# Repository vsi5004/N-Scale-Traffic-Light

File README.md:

# N-Scale-Traffic-Light
The PCB and 3D files for an accurately scaled 1:160 traffic light

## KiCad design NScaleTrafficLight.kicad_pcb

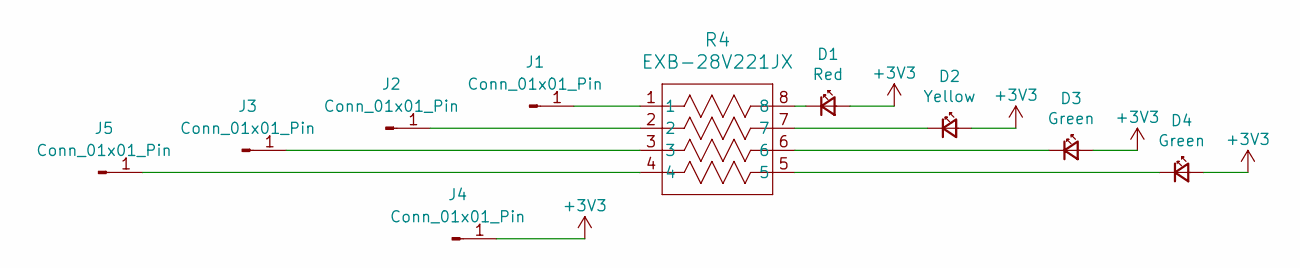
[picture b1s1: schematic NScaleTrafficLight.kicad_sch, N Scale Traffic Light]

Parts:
D1: Red; LED_0402_1005Metric; Mouser 710-150060VS55040
D2: Yellow; LED_0402_1005Metric; Mouser 710-150060VS55040
D3, D4: Green; LED_0402_1005Metric; Mouser 710-150060VS55040
J1, J2, J3, J4, J5: Conn_01x01_Pin; SolderWirePad_1x01_SMD_1x2mm
R4: EXB-28V221JX; EXB28V_PAN

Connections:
+3V3: D1.2 (A), D2.2 (A), D3.2 (A), D4.2 (A), J4.1
unnamed: D1.1 (K), R4.8
unnamed: D2.1 (K), R4.7
unnamed: D3.1 (K), R4.6
unnamed: D4.1 (K), R4.5
unnamed: J1.1, R4.1
unnamed: J2.1, R4.2
unnamed: J3.1, R4.3
unnamed: J5.1, R4.4

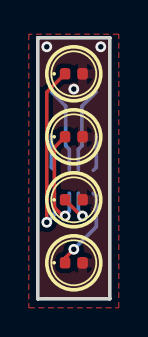
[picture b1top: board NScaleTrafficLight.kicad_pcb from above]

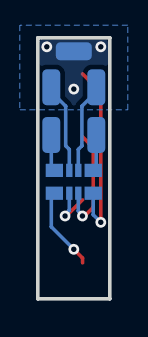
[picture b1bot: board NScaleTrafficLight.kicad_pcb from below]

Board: 2 copper layers, 4.0 x 14.5 mm, 10 parts (6 on the bottom side), 9 nets.

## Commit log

2024-09-26 Create V1 of PCB and Scematic
2024-09-27 Add resistor network, 4th signal light option
